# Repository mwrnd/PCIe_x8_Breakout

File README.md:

# PCIe_x8_Breakout

PCIe x8 Signal Breakout to [U.FL/UMCC Connectors](https://en.wikipedia.org/wiki/Hirose_U.FL).

[PCIEX1-SMA](https://github.com/teknoman117/PCIEX1-SMA/tree/f63db3cca1db83d9b58e01254d8104f65855b762) is a similar project that is PCIe x1 and uses SMA connectors.

The board requires up to 34 [U.FL/UMCC Surface Mount Receptacles](https://www.digikey.com/en/products/detail/te-connectivity-amp-connectors/2337019-1/9974052) and a 16-Pin 2.54mm [Header](https://www.digikey.com/en/products/detail/sullins-connector-solutions/PREC008DAAN-RC/2774886) or [Socket](https://www.digikey.com/en/products/detail/adam-tech/RS2-16-G/9832058).

Related Projects: [OpenCAPI_Breakout](https://github.com/mwrnd/OpenCAPI_Breakout), [OpenCAPI-to-PCIe](https://github.com/mwrnd/OpenCAPI-to-PCIe), [OpenCAPI-to-PCIe_x4_Host_and_Endpoint](https://github.com/mwrnd/OpenCAPI-to-PCIe_x4_Host_and_Endpoint)

# Testing and Use Example

The board is currently being used along with an [OpenCAPI_Breakout](https://github.com/mwrnd/OpenCAPI_Breakout) board to test [OpenCAPI-to-PCIe](https://github.com/mwrnd/innova2_experiments/tree/main/xdma_opencapi) on the [Innova-2 SmartNIC](https://www.nvidia.com/en-us/networking/ethernet/innova-2-flex/). PCIe 3.0 x4 at 8.0GT/s is currently working. Standard [0.1" M-F Jumpers](https://www.digikey.com/en/products/detail/adafruit-industries-llc/1954/6827087) are used for the PCIe Reset Signal (*nPERST*) and its GND.

With cables shorter than 4"~=100mm the [adapters work](https://github.com/mwrnd/innova2_experiments/tree/main/xdma_opencapi). Note the [RX U.FL-to-U.FL cables](https://www.digikey.com/en/products/detail/te-connectivity-amp-connectors/2118651-6/11205742) are all the same length as each other and likewise all [TX cables](https://www.digikey.com/en/products/detail/te-connectivity-amp-connectors/2015698-2/1249186) are the same length but RX and TX are different lengths as that is what I had access to. RX on the PCIe board connects to RX on the OpenCAPI board as it uses the OpenCAPI Host pinout. 

PCIe x4 In-system:

However, using 250mm IPEX cables the adapters fail for PCIe x8:

PCIe x8 In-system:

# PCB Layout

All signals are length-matched to within 1mm both inter-pair and intra-pair.

Resistor footprint R1 connects `PRSNT1` to `PRSNT2_x8`. The R1 trace can be cut and `PRSNT1` can be connected to a different `PRSNT2` to reduce the [PCIe lane width](https://en.wikipedia.org/wiki/PCI_Express#Lane).

Wire jumpers can then be used to connect `PRSNT1` to any of the `PRSNT2`.

# Schematic

# PCB Layer Stackup

4-Layer PCB stackup taken from [JLCPCB](https://jlcpcb.com/capabilities/pcb-capabilities).

Differential Impedance parameters were calculated using the [DigiKey Online Calculator](https://www.digikey.com/en/resources/conversion-calculators/conversion-calculator-pcb-trace-impedance).

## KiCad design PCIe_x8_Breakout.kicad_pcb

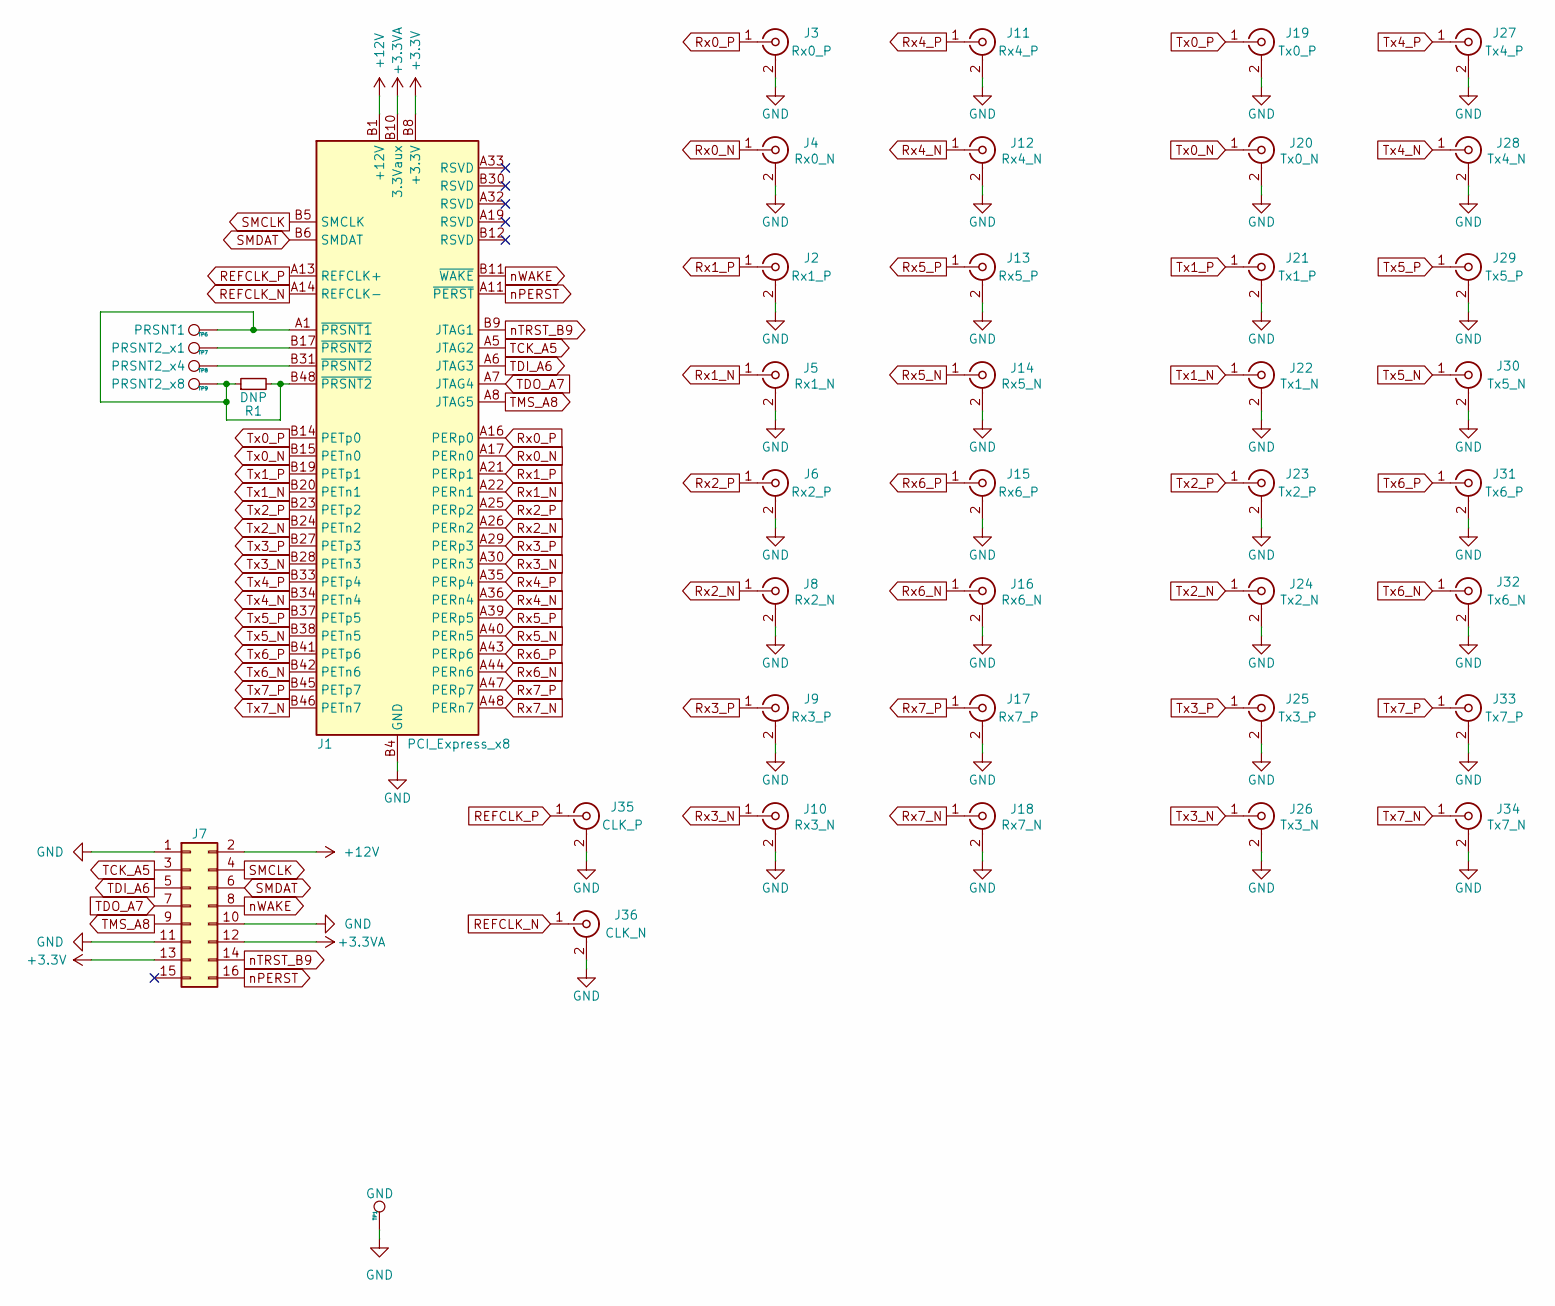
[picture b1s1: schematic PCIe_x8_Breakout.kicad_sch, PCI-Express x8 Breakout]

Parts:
J1: PCI_Express_x8; BUS_PCIexpress_x8
J2: Rx1_P; U.FL_Hirose_w_Label
J3: Rx0_P; U.FL_Hirose_w_Label
J4: Rx0_N; U.FL_Hirose_w_Label
J5: Rx1_N; U.FL_Hirose_w_Label
J6: Rx2_P; U.FL_Hirose_w_Label
J7: Conn_02x08_Odd_Even; PinSocket_2x08_P2.54mm_Vertical
J8: Rx2_N; U.FL_Hirose_w_Label
J9: Rx3_P; U.FL_Hirose_w_Label
J10: Rx3_N; U.FL_Hirose_w_Label
J11: Rx4_P; U.FL_Hirose_w_Label
J12: Rx4_N; U.FL_Hirose_w_Label
J13: Rx5_P; U.FL_Hirose_w_Label
J14: Rx5_N; U.FL_Hirose_w_Label
J15: Rx6_P; U.FL_Hirose_w_Label
J16: Rx6_N; U.FL_Hirose_w_Label
J17: Rx7_P; U.FL_Hirose_w_Label
J18: Rx7_N; U.FL_Hirose_w_Label
J19: Tx0_P; U.FL_Hirose_w_Label
J20: Tx0_N; U.FL_Hirose_w_Label
J21: Tx1_P; U.FL_Hirose_w_Label
J22: Tx1_N; U.FL_Hirose_w_Label
J23: Tx2_P; U.FL_Hirose_w_Label
J24: Tx2_N; U.FL_Hirose_w_Label
J25: Tx3_P; U.FL_Hirose_w_Label
J26: Tx3_N; U.FL_Hirose_w_Label
J27: Tx4_P; U.FL_Hirose_w_Label
J28: Tx4_N; U.FL_Hirose_w_Label
J29: Tx5_P; U.FL_Hirose_w_Label
J30: Tx5_N; U.FL_Hirose_w_Label
J31: Tx6_P; U.FL_Hirose_w_Label
J32: Tx6_N; U.FL_Hirose_w_Label
J33: Tx7_P; U.FL_Hirose_w_Label
J34: Tx7_N; U.FL_Hirose_w_Label
J35: CLK_P; U.FL_Hirose_w_Label
J36: CLK_N; U.FL_Hirose_w_Label
R1: DNP; R_0603_1608Metric
TP1: GND; PinSocket_1x01_P2.54mm_Vertical
TP6: PRSNT1; PinHeader_1x01_P1.00mm_Vertical
TP7: PRSNT2_x1; PinHeader_1x01_P1.00mm_Vertical
TP8: PRSNT2_x4; PinHeader_1x01_P1.00mm_Vertical
TP9: PRSNT2_x8; PinHeader_1x01_P1.00mm_Vertical

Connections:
+3.3V: J1.A9 (+3.3V), J1.A10 (+3.3V), J1.B8 (+3.3V), J7.13
+3.3VA: J1.B10 (3.3Vaux), J7.12
+12V: J1.A2 (+12V), J1.A3 (+12V), J1.B1 (+12V), J1.B2 (+12V), J1.B3 (+12V), J7.2
GND: J1.A4 (GND), J1.A12 (GND), J1.A15 (GND), J1.A18 (GND), J1.A20 (GND), J1.A23 (GND), J1.A24 (GND), J1.A27 (GND), J1.A28 (GND), J1.A31 (GND), J1.A34 (GND), J1.A37 (GND), J1.A38 (GND), J1.A41 (GND), J1.A42 (GND), J1.A45 (GND), J1.A46 (GND), J1.A49 (GND), J1.B4 (GND), J1.B7 (GND), J1.B13 (GND), J1.B16 (GND), J1.B18 (GND), J1.B21 (GND), J1.B22 (GND), J1.B25 (GND), J1.B26 (GND), J1.B29 (GND), J1.B32 (GND), J1.B35 (GND), J1.B36 (GND), J1.B39 (GND), J1.B40 (GND), J1.B43 (GND), J1.B44 (GND), J1.B47 (GND), J1.B49 (GND), J2.2 (Ext), J3.2 (Ext), J4.2 (Ext), J5.2 (Ext), J6.2 (Ext), J7.1, J7.10, J7.11, J8.2 (Ext), J9.2 (Ext), J10.2 (Ext), J11.2 (Ext), J12.2 (Ext), J13.2 (Ext), J14.2 (Ext), J15.2 (Ext), J16.2 (Ext), J17.2 (Ext), J18.2 (Ext), J19.2 (Ext), J20.2 (Ext), J21.2 (Ext), J22.2 (Ext), J23.2 (Ext), J24.2 (Ext), J25.2 (Ext), J26.2 (Ext), J27.2 (Ext), J28.2 (Ext), J29.2 (Ext), J30.2 (Ext), J31.2 (Ext), J32.2 (Ext), J33.2 (Ext), J34.2 (Ext), J35.2 (Ext), J36.2 (Ext), TP1.1
unnamed: J1.A1 (~PRSNT1), J1.B48 (~PRSNT2), R1.1, R1.2, TP6.1, TP9.1
unnamed: J1.B17 (~PRSNT2), TP7.1
unnamed: J1.B31 (~PRSNT2), TP8.1
REFCLK_N: J1.A14 (REFCLK-), J36.1 (In)
REFCLK_P: J1.A13 (REFCLK+), J35.1 (In)
Rx0_N: J1.A17 (PERn0), J4.1 (In)
Rx0_P: J1.A16 (PERp0), J3.1 (In)
Rx1_N: J1.A22 (PERn1), J5.1 (In)
Rx1_P: J1.A21 (PERp1), J2.1 (In)
Rx2_N: J1.A26 (PERn2), J8.1 (In)
Rx2_P: J1.A25 (PERp2), J6.1 (In)
Rx3_N: J1.A30 (PERn3), J10.1 (In)
Rx3_P: J1.A29 (PERp3), J9.1 (In)
Rx4_N: J1.A36 (PERn4), J12.1 (In)
Rx4_P: J1.A35 (PERp4), J11.1 (In)
Rx5_N: J1.A40 (PERn5), J14.1 (In)
Rx5_P: J1.A39 (PERp5), J13.1 (In)
Rx6_N: J1.A44 (PERn6), J16.1 (In)
Rx6_P: J1.A43 (PERp6), J15.1 (In)
Rx7_N: J1.A48 (PERn7), J18.1 (In)
Rx7_P: J1.A47 (PERp7), J17.1 (In)
SMCLK: J1.B5 (SMCLK), J7.4
SMDAT: J1.B6 (SMDAT), J7.6
TCK_A5: J1.A5 (JTAG2), J7.3
TDI_A6: J1.A6 (JTAG3), J7.5
TDO_A7: J1.A7 (JTAG4), J7.7
TMS_A8: J1.A8 (JTAG5), J7.9
Tx0_N: J1.B15 (PETn0), J20.1 (In)
Tx0_P: J1.B14 (PETp0), J19.1 (In)
Tx1_N: J1.B20 (PETn1), J22.1 (In)
Tx1_P: J1.B19 (PETp1), J21.1 (In)
Tx2_N: J1.B24 (PETn2), J24.1 (In)
Tx2_P: J1.B23 (PETp2), J23.1 (In)
Tx3_N: J1.B28 (PETn3), J26.1 (In)
Tx3_P: J1.B27 (PETp3), J25.1 (In)
Tx4_N: J1.B34 (PETn4), J28.1 (In)
Tx4_P: J1.B33 (PETp4), J27.1 (In)
Tx5_N: J1.B38 (PETn5), J30.1 (In)
Tx5_P: J1.B37 (PETp5), J29.1 (In)
Tx6_N: J1.B42 (PETn6), J32.1 (In)
Tx6_P: J1.B41 (PETp6), J31.1 (In)
Tx7_N: J1.B46 (PETn7), J34.1 (In)
Tx7_P: J1.B45 (PETp7), J33.1 (In)
nPERST: J1.A11 (~PERST), J7.16
nTRST_B9: J1.B9 (JTAG1), J7.14
nWAKE: J1.B11 (~WAKE), J7.8

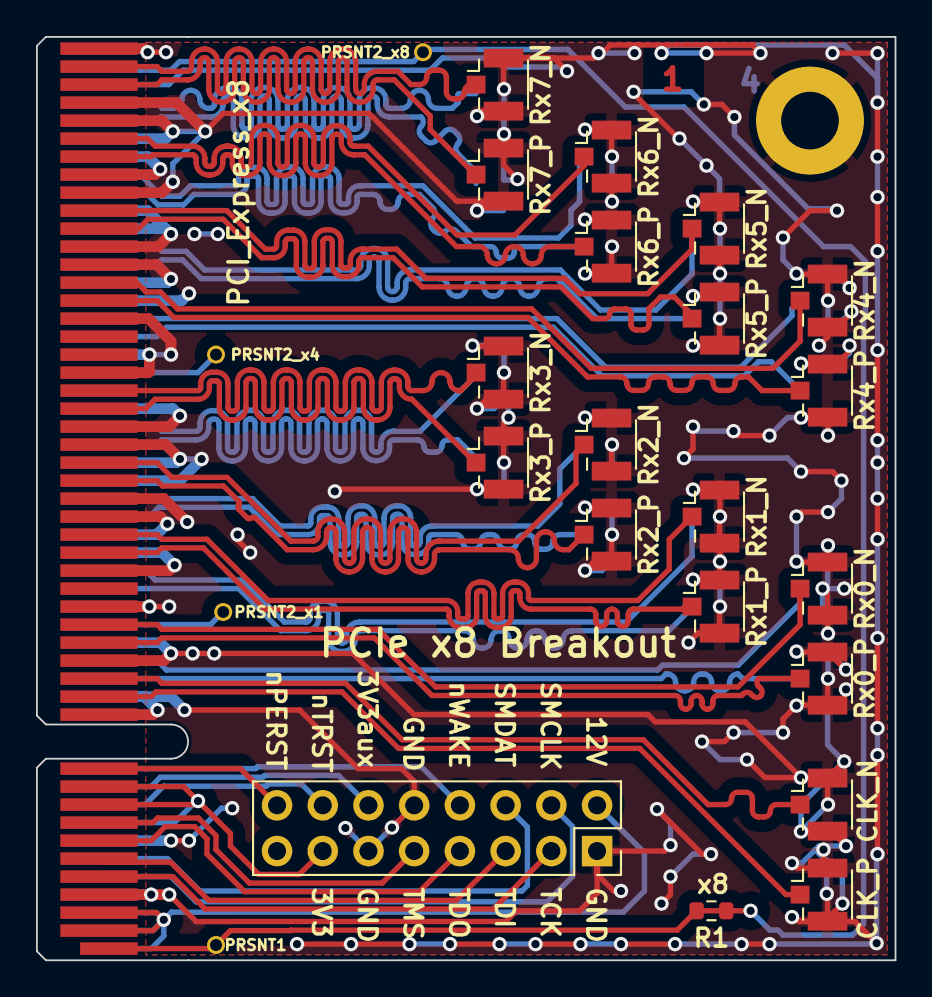
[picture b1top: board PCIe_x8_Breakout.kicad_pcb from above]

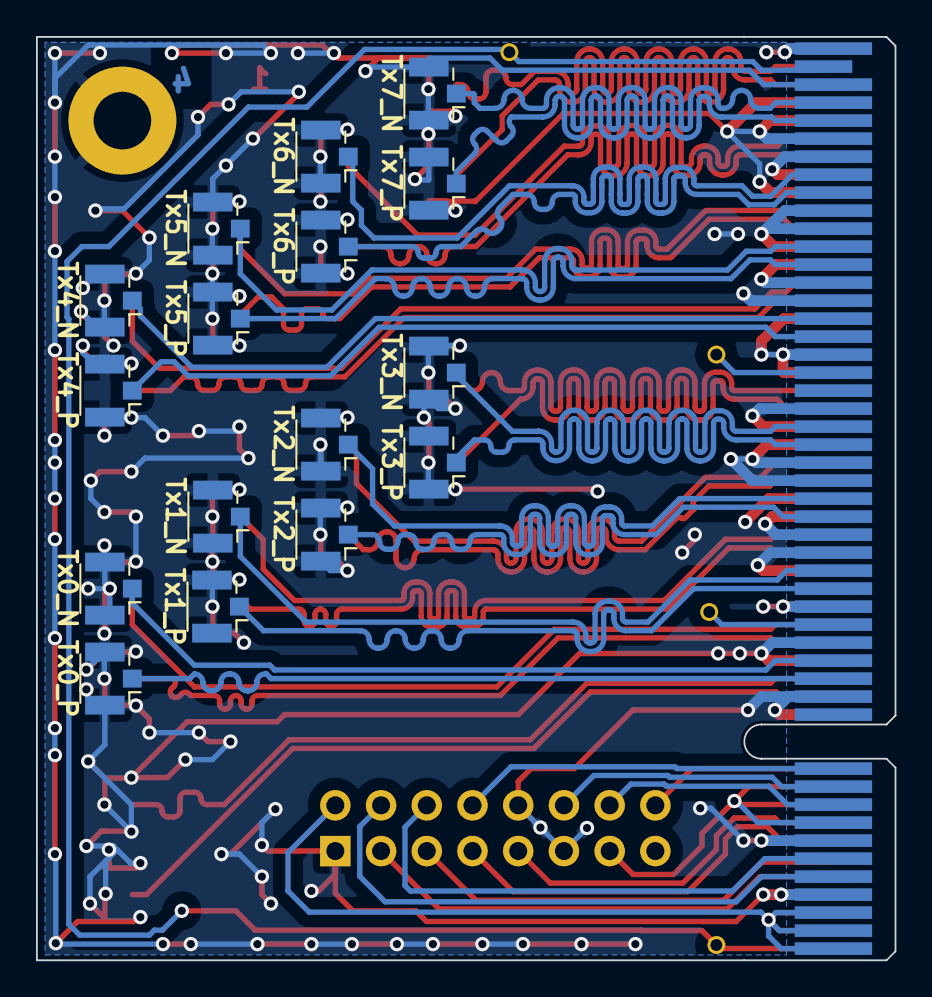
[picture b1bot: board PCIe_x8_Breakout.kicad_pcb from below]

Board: 4 copper layers, 47.7 x 51.3 mm, 42 parts (17 on the bottom side), 50 nets.

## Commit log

2023-06-10 First Revision
2023-11-12 Added In-System Usage Pictures
2023-11-28 PCIe x8 Update
